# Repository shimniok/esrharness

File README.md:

# Capacitor ESR test harness

Bad capacitors, if they aren't shorted or open, typically fail with a high equivalent series resistance (ESR).
You can measure ESR by building Stephen M. Powell's ESR test harness and an oscilloscope. The circuit and layout
are included, as well as information on an enclosure and front panel.

The way it works is the device sends a small, high frequency square wave through a capacitor--it can be on a
circuit board or off--and looking at the peak voltage drop of the wave form on an oscilloscope.

Write-up on my blog: http://www.bot-thoughts.com/2009/11/esr-test-harness.html

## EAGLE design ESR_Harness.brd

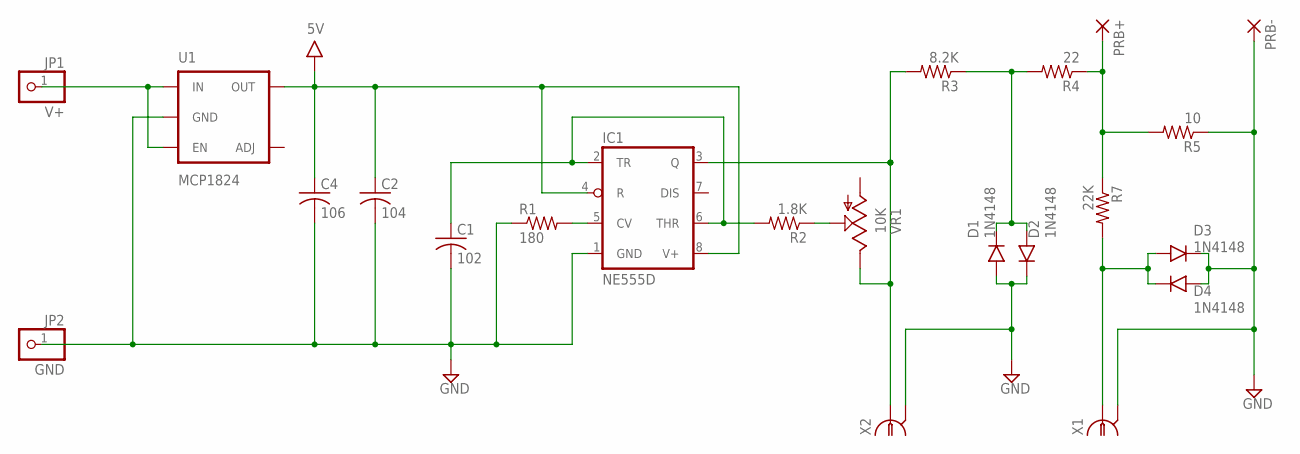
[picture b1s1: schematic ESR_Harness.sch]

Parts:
C1: 102; C0603
C2: 104; C0603
C4: 106; C1206
D1, D2, D3, D4: 1N4148; SOD123FL
IC1: NE555D; SO08
JP1: V+; 1X01-S
JP2: GND; 1X01-S
PRB+: WIREPAD3,17/1,3; 3,17/1,3
PRB-: WIREPAD3,17/1,3; 3,17/1,3
R1: 180; R0603
R2: 1.8K; R0603
R3: 8.2K; R0603
R4: 22; R0603
R5: 10; R0603
R7: 22K; R0603
U1: MCP1824; SOT23-5
VR1: 10K; OFFBOARD_POT_3
X1, X2: OFFBOARD_BNC; OFFBOARD_COAX

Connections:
5V: C2.1, C4.1, IC1.4 (R), IC1.8 (V+), U1.5 (OUT)
GND: C1.2, C2.2, C4.2, D1.A, D2.C, D3.C, D4.A, IC1.1 (GND), JP2.1, PRB-.1, R1.1, R5.1, U1.2 (GND), X1.P$GND (GND), X2.P$GND (GND)
unnamed: C1.1, IC1.2 (TR), IC1.6 (THR), R2.2
unnamed: IC1.5 (CV), R1.2
unnamed: R2.1, VR1.P$2 (S)
unnamed: PRB+.1, R4.1, R5.2, R7.1
unnamed: JP1.1, U1.1 (IN), U1.3 (EN)
unnamed: D1.C, D2.A, R3.1, R4.2
unnamed: D3.A, D4.C, R7.2, X1.P$1 (1)
unnamed: IC1.3 (Q), R3.2, VR1.P$3 (E), X2.P$1 (1)

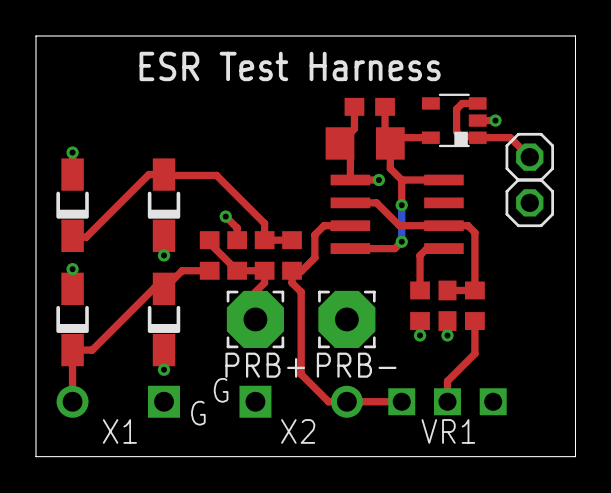
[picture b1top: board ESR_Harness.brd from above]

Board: 2 copper layers, 30.0 x 23.4 mm, 22 parts (0 on the bottom side), 10 nets.

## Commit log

2015-09-21 Additional files
2015-09-21 renamed bmp file
2015-09-21 Initial cut at smt
2021-02-12 updated gitignore
